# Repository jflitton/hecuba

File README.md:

# Hecuba

A read-only imager for Priam DISKOS 8-inch Winchester drives, talking to the
drive over its native PRIAM 50-pin interface. Three parts: a small interface
board, firmware for the Raspberry Pi Pico 2 W that plugs into it, and host-side
Python tools that image the drive, recover damaged sectors offline, and walk
the recovered filesystem.

It was built to recover a Priam 3450 pulled from an Intel Multibus development
system (iSBC 215 controller, iRMX-86), and has imaged that drive in full. The
name: Hecuba was queen of Troy and wife of Priam.

## For data preservationists

If you have a Priam DISKOS 8-inch drive (a 3450, or likely a 7050) whose
contents you want to archive, email <jeff@flitton.dev>. I have a handful of
assembled Hecuba boards and can send you one. I am also glad to help with the
imaging and recovery, and to answer questions about the drive or its interface.

## Layout

| Directory | Contents | README |
|---|---|---|
| `hardware/` | KiCad project for the interface board: schematic, layout, BOM, measured termination values, 50-pin pinout | [hardware/README.md](hardware/README.md) |
| `firmware/` | Pico 2 W firmware: PRIAM register bus, PIO/DMA track capture, USB serial console | [firmware/README.md](firmware/README.md) |
| `software/` | Host tools: whole-drive imaging, three offline recovery passes, iSBC 215 sector decoder, iRMX-86 filesystem walker, defect map | [software/README.md](software/README.md) |

## Why it exists

These drives have a unique interface that resembles SASI at first glance but
is distinctly different.

- The heads move only on the drive's own command. There is no STEP line; a seek
  is a register write over the ribbon. The drive must be powered, spun up, and
  answering before it will read anything.
- The interface is recovered NRZ data plus clock on RS-422 pairs at 6.4 Mbit/s,
  not raw flux. A flux imager has nothing to read.

Acquisition and decoding are kept separate: capture each track once, cleanly,
then decode and repair offline, minimizing drive wear.

## Workflow

1. Build the board (`hardware/`). Rev 0.9A is fabricated and assembled.
2. Build and flash the firmware (`firmware/`), then bring the drive up from the
   USB serial console: `up`, `id`, `pins`, `stair`.
3. Image the drive with `software/sweep.py`, which drives that console and
   writes per-track sector images plus every raw capture.
4. Recover remaining sectors offline with `vote_repair.py`, `rescue.py`, and
   `deep_rescue.py`.
5. Walk the volume with `irmx_fs.py`, and attribute unrecovered sectors with
   `defect_map.py`.

## Read-only

The board has no copper on the write lines, and the firmware has no code path
that asserts WRITE GATE. Writing to a disk would require modifying the board.

## Scope

The sector decoder and filesystem walker target what this drive held: the Intel
iSBC 215 512-byte sector format and iRMX-86 named volumes. The board and
firmware are format-agnostic and capture raw bits from any drive with the PRIAM
interface. Termination values in `hardware/` were measured on one drive;
measure yours before populating.

Only the DISKOS 3450 has been tested. The DISKOS 7050 shares the same
interface, electrical spec, and service manual, so the board and firmware
should work on it as well, unconfirmed. The 7050 has 1049 cylinders to the
3450's 525, and that count is hardcoded in `firmware/include/priam_proto.h`
and `software/sweep.py`; the `id` command also expects the 3450's ID code.

No disk contents are part of this repository.

## License

The firmware and software are released under the MIT License, see
[LICENSE](LICENSE). The hardware design under `hardware/` is released under the
CERN Open Hardware Licence Version 2, Permissive (CERN-OHL-P-2.0), see
[hardware/LICENSE](hardware/LICENSE).

Both licenses allow commercial use, and both require that the copyright notice
and license text stay with copies and derived works. Both disclaim all
warranties: the software, the firmware, the design files, and any board built
from them are provided as is, and the risk of building and using them is
yours. Vendor symbol and footprint files under `hardware/lib/` are Texas
Instruments' and are not covered by either license.

## Reference documents

- [Priam 8-inch Winchester maintenance manual, July 1982](https://bitsavers.org/pdf/priam/Priam8_Maint_Jul82.pdf),
  and its [drawings volume](https://bitsavers.org/pdf/priam/Priam8_Maint_Drawings_Jul82.pdf)
  (schematics; an [800 dpi scan](https://bitsavers.org/pdf/priam/Priam8_Maint_Drawings_800dpi_Jul82.pdf) is also there)
- [Intel iSBC 215 Winchester Disk Controller Hardware Reference Manual,
  121593-002, September 1981](https://bitsavers.org/pdf/intel/iSBC/121593-002_iSBC_215_Winchester_Disk_Controller_Hardware_Reference_Manual_Sep1981.pdf)
- David Gesswein's excellent [mfm](https://www.pdp8online.com/mfm/) project, which documents the iSBC 215 sector format

## Author

Jeff Flitton, <jeff@flitton.dev>

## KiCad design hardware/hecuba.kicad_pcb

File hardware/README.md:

# Hecuba hardware

KiCad project for the Hecuba interface board. It sits between a Priam DISKOS
8-inch Winchester drive's native 50-pin interface and a Raspberry Pi Pico 2 W
(ref `A1`), which runs the firmware in `../firmware`. Rev 0.9A is fabricated,
assembled, and has imaged a full Priam 3450. Read-only by design.

## Why a custom board

The Priam 3450 (about 35 MB, 3,600 RPM, 5 heads, 525 cylinders) fits none of
the usual readers.

- No STEP line. Heads are positioned by a closed-loop voice-coil servo under an
  on-board 8035. A seek is a register write plus a Seek command, and the drive
  must be powered, spun up, and taking commands before it returns a bit.
- Not a flux interface. The drive does its own data separation and outputs
  recovered NRZ data plus clock on RS-422 pairs at 6.4 Mbit/s.
- The sector format belongs to the controller that wrote the disk (an Intel
  iSBC 215 here), not to the drive. Decoding happens offline in `../software`.
- Not SASI, despite the 50-pin ribbon and 8-bit active-low bus. PRIAM has no
  REQ/ACK handshake and carries read data on separate differential pairs.

## Building one

| | |
|---|---|
| Board | 2 layers, 125 x 104 mm, 1.6 mm. Signals on top; bottom is a ground pour with +5 V and +3.3 V routed through it as 1 mm paths |
| Tracks and vias | 0.2 mm signal, 1.0 mm power. Vias 0.6 mm / 0.3 mm hole (1.0 / 0.6 on power) |
| Smallest features | 0.2 mm track, 0.3 mm hole, 0.5 mm copper to edge |
| Packages | SOIC and SOT-23-6 ICs, 0805 passives. Hand-solderable in about an hour |
| Mounting | Four 3 mm plated holes, grounded |
| Parts list | `bom/bom.csv`, with a column for parts deliberately left unpopulated |
| Placement guide | `bom/ibom.html`, interactive; click a part to see where it goes |

All ICs are current-production TI parts as of 2026. Gerbers are plotted from
KiCad when needed and are not committed.

Routing rules for a respin:

- Only READ DATA and READ/REF CLOCK need care. Route each as a tight parallel
  pair over unbroken ground, and keep the two pairs apart. No impedance control
  and no length matching (the skew budget at 6.4 Mbit/s is about 170 mm).
- Everything else is slow. Keep the 8 data-bus lines grouped.
- Damping resistors at the source, termination at the receiver, and each
  100 nF capacitor hard against its power pin with its own ground via.

## Parts

| Ref | Part | Function | Datasheet |
|---|---|---|---|
| A1 | Pico 2 W (RP2350) | Controller. Powers the board over USB | [raspberrypi.com](https://datasheets.raspberrypi.com/picow/pico-2-w-datasheet.pdf) |
| U1 | SN74LVC4245A | 8-bit data bus, bidirectional. Direction set by the Pico (GP8) | [ti.com](https://www.ti.com/lit/ds/symlink/sn74lvc4245a.pdf) |
| U2 | SN74LVC4245A | Outbound control lines: address, strobes, head select, read gate. Direction strapped | [ti.com](https://www.ti.com/lit/ds/symlink/sn74lvc4245a.pdf) |
| U3 | SN74LVC14A | Schmitt-trigger inverters on INDEX, READY, SECTOR MARK | [ti.com](https://www.ti.com/lit/ds/symlink/sn74lvc14a.pdf) |
| U4 | AM26LV32E | RS-422 receivers for READ DATA and READ/REF CLOCK. Receive only | [ti.com](https://www.ti.com/lit/ds/symlink/am26lv32e.pdf) |
| U5 | SN74LVC1T45 | -RESET driver. Direction strapped | [ti.com](https://www.ti.com/lit/ds/symlink/sn74lvc1t45.pdf) |
| J1 | 2x25 IDC header | 50-pin ribbon to the drive | |

## Termination

Measured on one drive. Measure yours before populating. The manual's generic
values assume the controller terminates everything; this drive terminates most
of the bus internally. Values were measured at the connector with the drive
unpowered and the ribbon off.

| Part | Value | Fitted | Reason |
|---|---|---|---|
| R1-R16, R28 | 0 ohm | yes | Series damping on outbound lines. The drive terminates this bus at about 179 ohm; even 33 ohm in series lifts a logic low to about 0.72 V against a 0.8 V threshold. Fit 10 ohm or less only if a scope shows overshoot |
| R17 / R20 | 220 / 330 ohm | yes | INDEX pull-up and pull-down. INDEX measured open at the drive. Settles near 3.0 V released |
| R18-R19 / R21-R22 | 220 / 330 ohm | no | READY and SECTOR MARK are pulled up inside the drive (130 / 175 ohm measured). Fit only if J1 pin 28 is left unpowered |
| R26 | 1 k | yes | Bias across the CLOCK pair, which measured 95 ohm. 100 ohm here would load the pair to 49 ohm |
| R27 | 100 ohm | yes | Termination across the DATA pair, which measured 252 ohm |
| R29 | 10 k | yes | Pull-up on GP17 (-RESET). Holds reset deasserted through boot |
| C1-C8 | 100 nF | yes | Decoupling, one per power pin |
| C9 / C10 | 10 uF | yes | Bulk on each rail at the Pico's power pins |
| JP1 | 2-pin header | shunt open | +5 V to J1 pin 28 (terminator power). Not needed on the drive tested |

## 50-pin connector (J1)

| Signal | Pin | Direction | Connects to |
|---|---|---|---|
| DBUS 0-7 | 2-9 | both | U1 via R1-R8 |
| -READ GATE | 11 | to drive | U2 via R9 |
| -RESET | 13 | to drive | U5 via R28 |
| -WRITE GATE | 15 | to drive | not connected |
| -RD / -WR | 17 / 18 | to drive | U2 via R10 / R11 |
| +AD 1 / +AD 0 | 19 / 20 | to drive | U2 via R12 / R13 |
| -DRIVE SELECT 1 | 22 | to drive | ground (always selected) |
| -DRIVE SELECT 2-4 | 23-25 | to drive | not connected |
| +5 V to terminator | 28 | power | JP1 (open) |
| -HEAD SELECT 4 / 2 / 1 | 29 / 30 / 31 | to drive | U2 via R14 / R15 / R16 |
| -INDEX | 33 | from drive | U3, with R17 / R20 |
| -READY | 35 | from drive | U3 |
| -SECTOR MARK | 37 | from drive | U3 |
| WRITE DATA pair | 39 / 40 | to drive | not connected |
| WRITE CLOCK pair | 42 / 43 | to drive | not connected |
| READ/REF CLOCK pair | 45 / 46 | from drive | U4, R26 across |
| READ DATA pair | 48 / 49 | from drive | U4, R27 across |

Ground pins 1, 10, 12, 14, 16, 21, 26, 27, 32, 34, 36, 38, 41, 44, 47, 50
connect to the ground plane.

## Power

- Drive rails (+24 V, +5 V, -5 V, -12 V, about 100 W total) come from a bench
  supply into the drive's own connector. The board neither carries nor senses
  them. Current-limit and watch +24 V at power-up; it runs the spindle and the
  voice coil.
- Board rails come from the Pico's USB. VBUS (pin 40) feeds the drive-facing
  side of the translators and the status pull-ups. The Pico's 3.3 V regulator
  (pin 36) feeds the Pico-facing side.
- Board draw is about 250 mA idle and 400 to 600 mA peak (the radio spikes on
  transmit). Use a 1.5 A supply or powered hub.

Power the Pico first, then the drive, and do not replug USB while the drive is
powered. Until firmware init runs, the Pico's pins are inputs with pull-downs,
which asserts every active-low control line through U2. Only -RESET is
protected in hardware (R29).

## Noteworthy facts

- **Write lines have no copper.** WRITE GATE, WRITE DATA, and WRITE CLOCK
  appear on the connector symbol only. No trace, no resistor. Writing would
  require adding wires to the board. The drive's own Write Enable switch is
  also off, and its internal terminator holds WRITE GATE deasserted.
- **The drive is 5 V TTL; the RP2350 is 3.3 V and not 5 V tolerant.** Every
  signal crosses a translator. Net names carry the level: `DBUS0` on the drive
  side, `DBUS0_3V3` on the Pico side.
- **Status lines invert.** U3 inverts, so INDEX, READY, and SECTOR MARK read
  active-high at the Pico while every other PRIAM signal is active-low. The
  schematic writes active-low nets as `~{NAME}`; the drive manual uses a
  leading minus. The full per-line chain is in
  `../firmware/include/board_pins.h`.
- **U3 is a Schmitt trigger on purpose.** The drive's status outputs are
  open-collector 75462s with slow RC rising edges. Hysteresis turns each into
  one clean transition. The drive's own end uses 74LS14s for the same reason.
- **U4 is the E variant on purpose.** AM26LV32E adds hysteresis and an
  open-input fail-safe, so the read pairs hold a defined level before READ GATE
  asserts and before the drive's clock recovery locks.
- **R29 is load-bearing.** U5 has no output enable and follows GP17 from
  power-on, and the RP2350 boots GP17 as an input with a pull-down. Without
  R29 every power-up would reset the drive.
- **DRIVE SELECT 1 is tied to ground.** One drive, permanently selected, no
  chip-select GPIO. The data bus still only drives back during a read strobe.
- **Unused U3 and U4 inputs are tied off.** Floating Schmitt or differential
  inputs oscillate.
- **R26 and R27 differ by 10x** for two pairs on the same connector. Only
  measurement finds that.

## Files

| Path | Contents |
|---|---|
| `hecuba.kicad_pro` | Project settings, net classes, design rules |
| `hecuba.kicad_sch` | Schematic, one sheet |
| `hecuba.kicad_pcb` | Board layout |
| `hecuba.kicad_prl` | KiCad UI state |
| `hecuba.kicad_sym` | Five project symbols. `PRIAM_50` is the drive connector with real PRIAM signal names |
| `footprints.pretty/` | Footprints for the four ICs, registered by `fp-lib-table` so the project opens standalone |
| `fp-lib-table` | Points KiCad at the folder above |
| `lib/<PART>/` | Vendor symbol and footprint downloads per chip, untouched. Datasheets are linked from the parts table, not stored here |
| `bom/bom.csv` | Parts list with populate / do-not-populate column |
| `bom/ibom.html` | Interactive BOM |

`.gitignore` covers KiCad backups and netlist output.

## License

CERN Open Hardware Licence Version 2, Permissive (CERN-OHL-P-2.0). The full
text is in [LICENSE](LICENSE). Keep the copyright and license notices with any
copy or derivative of the design files, and on boards where practicable (the
silkscreen already carries the author line). The design is provided as is, with
no warranty, and the risk of building and using a board from it is yours.

Files under `lib/<PART>/` are Texas Instruments vendor downloads under TI's own
terms and are not covered by this license.

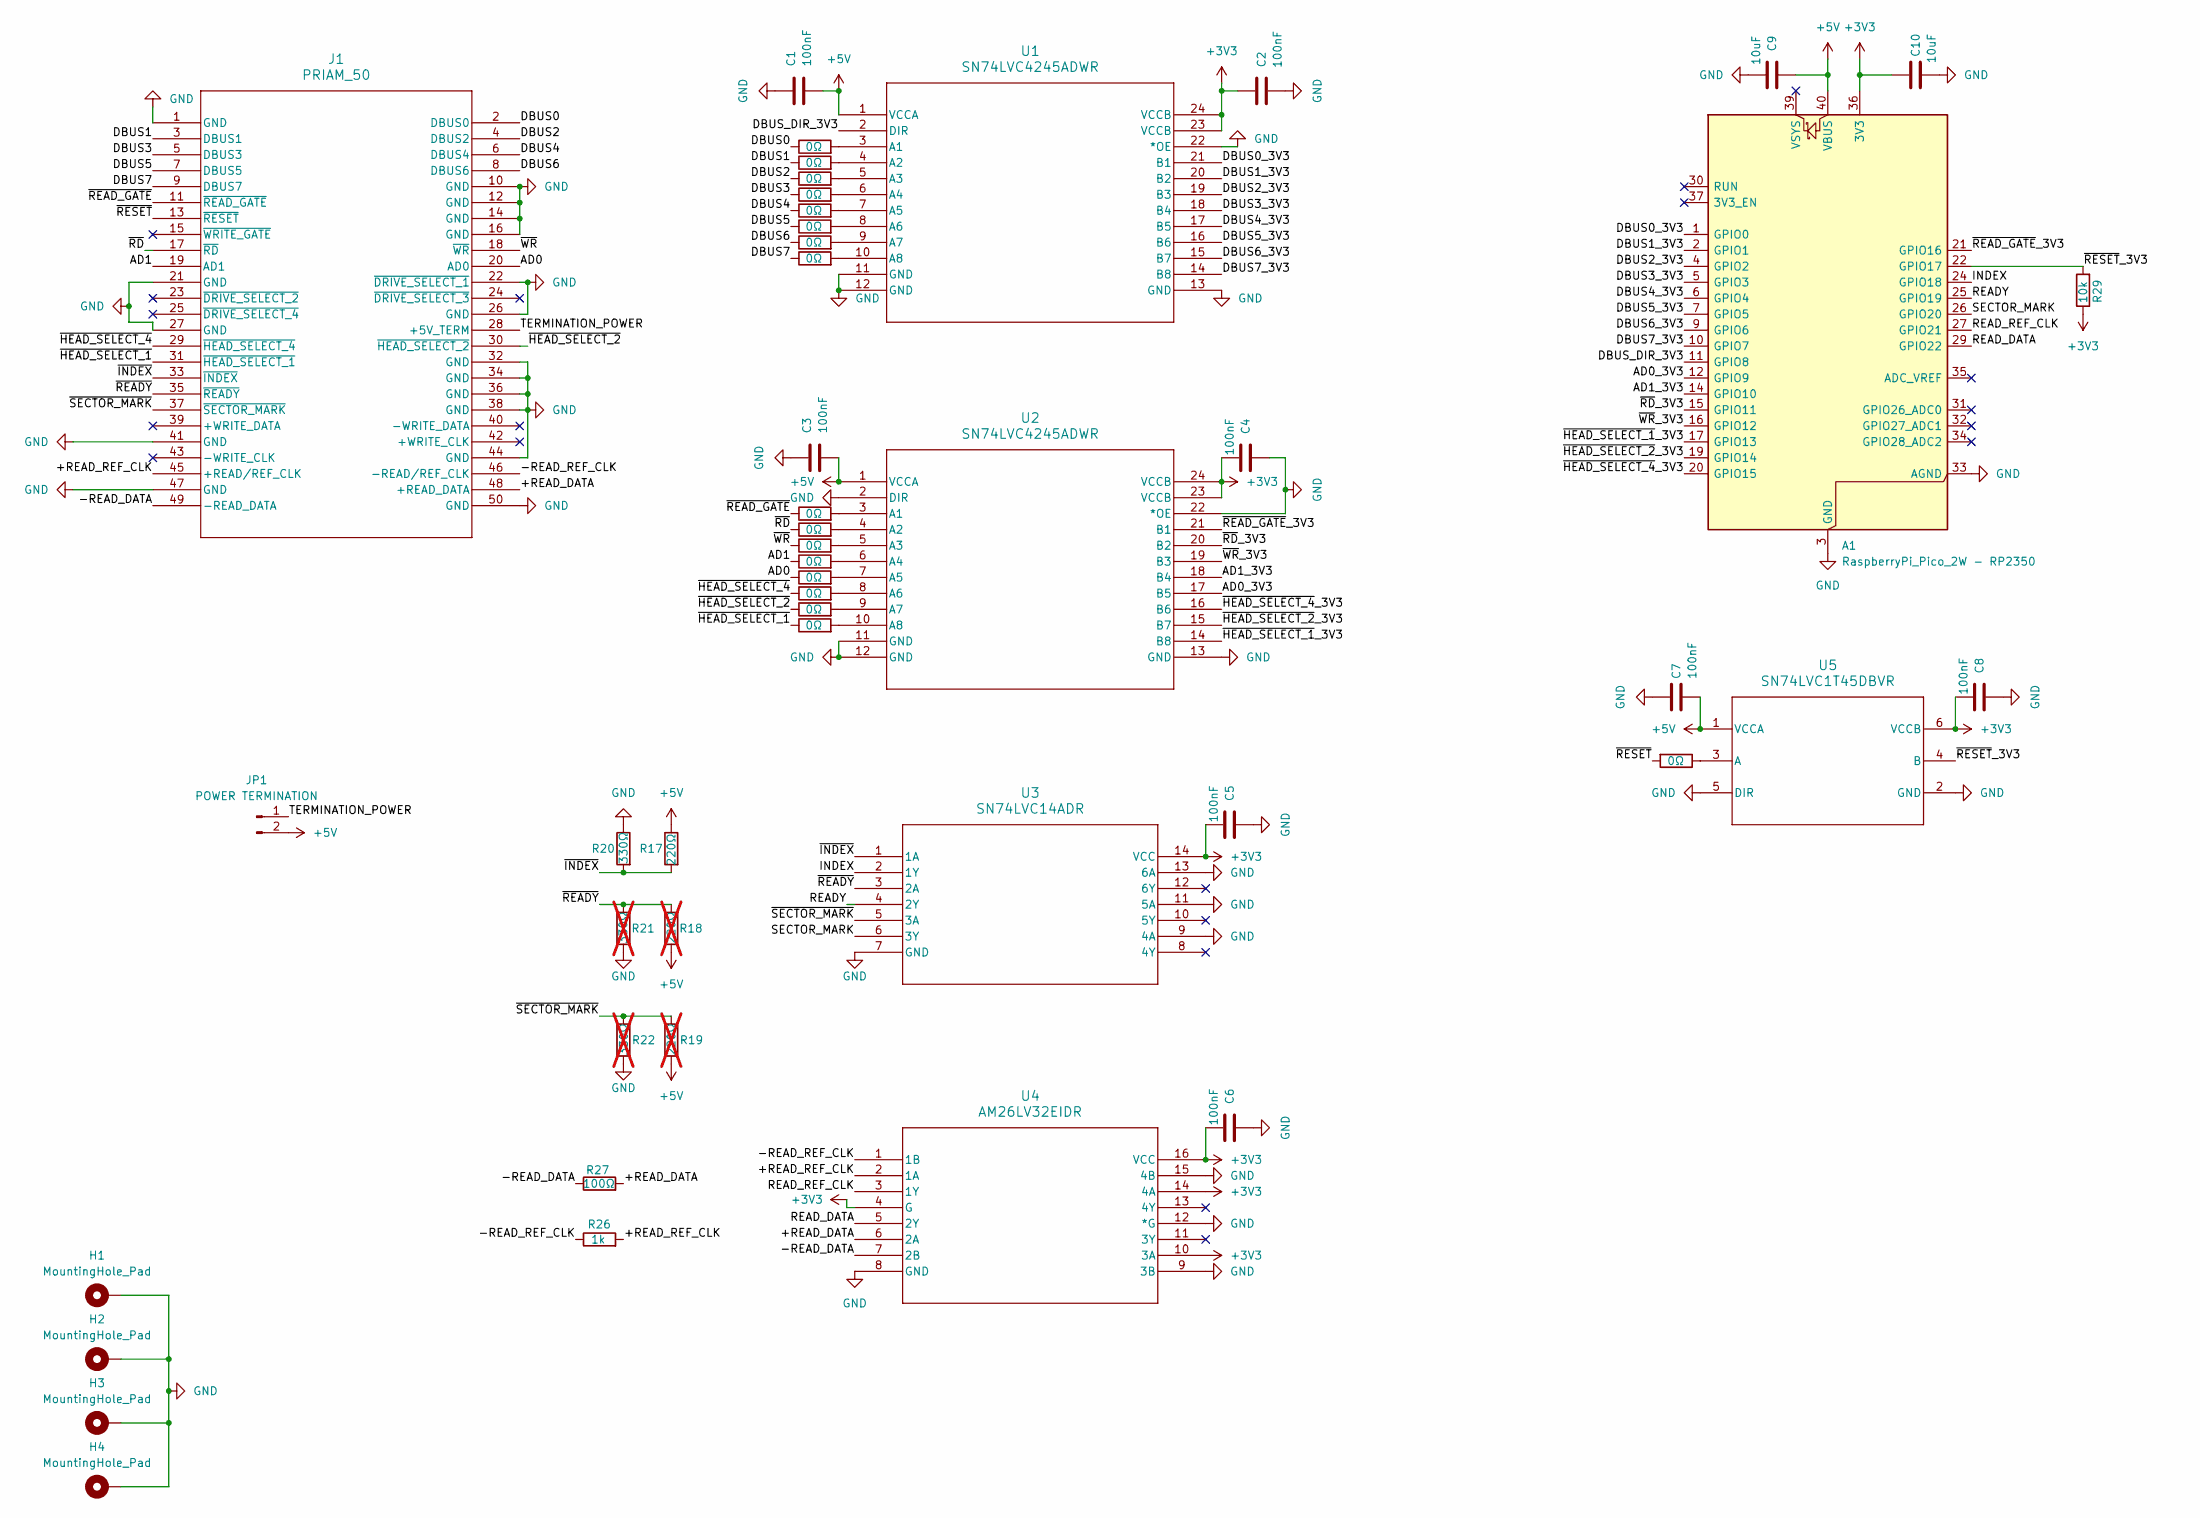
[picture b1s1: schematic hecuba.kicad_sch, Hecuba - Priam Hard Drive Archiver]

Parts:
A1: RaspberryPi_Pico_2W - RP2350; RaspberryPi_Pico_W_SMD_HandSolder
C1, C2, C3, C4, C5, C6, C7, C8: 100nF; C_0805_2012Metric_Pad1.18x1.45mm_HandSolder
C9, C10: 10uF; C_0805_2012Metric_Pad1.18x1.45mm_HandSolder
H1, H2, H3, H4: MountingHole_Pad; MountingHole_3mm_Pad
J1: PRIAM_50; IDC-Header_2x25_P2.54mm_Vertical
JP1: POWER TERMINATION; PinHeader_1x02_P2.54mm_Vertical
R1, R2, R3, R4, R5, R6, R7, R8, R9, R10, R11, R12, R13, R14, R15, R16, R28: 0Ω; R_0805_2012Metric_Pad1.20x1.40mm_HandSolder
R17: 220Ω; R_0805_2012Metric_Pad1.20x1.40mm_HandSolder
R18, R19: 220Ω; R_0805_2012Metric_Pad1.20x1.40mm_HandSolder; not fitted
R20: 330Ω; R_0805_2012Metric_Pad1.20x1.40mm_HandSolder
R21, R22: 330Ω; R_0805_2012Metric_Pad1.20x1.40mm_HandSolder; not fitted
R26: 1k; R_0805_2012Metric_Pad1.20x1.40mm_HandSolder
R27: 100Ω; R_0805_2012Metric_Pad1.20x1.40mm_HandSolder
R29: 10k; R_0805_2012Metric_Pad1.20x1.40mm_HandSolder
U1, U2: SN74LVC4245ADWR; DW24-M
U3: SN74LVC14ADR; D14-M
U4: AM26LV32EIDR; D16-M
U5: SN74LVC1T45DBVR; DBV0006A_M

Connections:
+3V3: A1.36 (3V3), C2.2, C4.2, C5.2, C6.2, C8.2, C10.1, R29.1, U1.23 (VCCB), U1.24 (VCCB), U2.23 (VCCB), U2.24 (VCCB), U3.14 (VCC), U4.4 (G), U4.10 (3A), U4.14 (4A), U4.16 (VCC), U5.6 (VCCB)
+5V: A1.40 (VBUS), C1.2, C3.2, C7.2, C9.1, JP1.2, R17.1, R18.2, R19.2, U1.1 (VCCA), U2.1 (VCCA), U5.1 (VCCA)
/+READ_DATA: J1.48 (+READ_DATA), R27.2, U4.6 (2A)
/+READ_REF_CLK: J1.45 (+READ/REF_CLK), R26.2, U4.2 (1A)
/-READ_DATA: J1.49 (-READ_DATA), R27.1, U4.7 (2B)
/-READ_REF_CLK: J1.46 (-READ/REF_CLK), R26.1, U4.1 (1B)
/AD0: J1.20 (AD0), R13.1
/AD0_3V3: A1.12 (GPIO9), U2.17 (B5)
/AD1: J1.19 (AD1), R12.1
/AD1_3V3: A1.14 (GPIO10), U2.18 (B4)
/DBUS0: J1.2 (DBUS0), R1.1
/DBUS0_3V3: A1.1 (GPIO0), U1.21 (B1)
/DBUS1: J1.3 (DBUS1), R2.1
/DBUS1_3V3: A1.2 (GPIO1), U1.20 (B2)
/DBUS2: J1.4 (DBUS2), R3.1
/DBUS2_3V3: A1.4 (GPIO2), U1.19 (B3)
/DBUS3: J1.5 (DBUS3), R4.1
/DBUS3_3V3: A1.5 (GPIO3), U1.18 (B4)
/DBUS4: J1.6 (DBUS4), R5.1
/DBUS4_3V3: A1.6 (GPIO4), U1.17 (B5)
/DBUS5: J1.7 (DBUS5), R6.1
/DBUS5_3V3: A1.7 (GPIO5), U1.16 (B6)
/DBUS6: J1.8 (DBUS6), R7.1
/DBUS6_3V3: A1.9 (GPIO6), U1.15 (B7)
/DBUS7: J1.9 (DBUS7), R8.1
/DBUS7_3V3: A1.10 (GPIO7), U1.14 (B8)
/DBUS_DIR_3V3: A1.11 (GPIO8), U1.2 (DIR)
/INDEX: A1.24 (GPIO18), U3.2 (1Y)
/READY: A1.25 (GPIO19), U3.4 (2Y)
/READ_DATA: A1.29 (GPIO22), U4.5 (2Y)
/READ_REF_CLK: A1.27 (GPIO21), U4.3 (1Y)
/SECTOR_MARK: A1.26 (GPIO20), U3.6 (3Y)
/TERMINATION_POWER: J1.28 (+5V_TERM), JP1.1
/~HEAD_SELECT_1: J1.31 (~HEAD_SELECT_1), R16.1
/~HEAD_SELECT_1_3V3: A1.17 (GPIO13), U2.14 (B8)
/~HEAD_SELECT_2: J1.30 (~HEAD_SELECT_2), R15.1
/~HEAD_SELECT_2_3V3: A1.19 (GPIO14), U2.15 (B7)
/~HEAD_SELECT_4: J1.29 (~HEAD_SELECT_4), R14.1
/~HEAD_SELECT_4_3V3: A1.20 (GPIO15), U2.16 (B6)
/~INDEX: J1.33 (~INDEX), R17.2, R20.2, U3.1 (1A)
/~RD: J1.17 (~RD), R10.1
/~RD_3V3: A1.15 (GPIO11), U2.20 (B2)
/~READY: J1.35 (~READY), R18.1, R21.1, U3.3 (2A)
/~READ_GATE: J1.11 (~READ_GATE), R9.1
/~READ_GATE_3V3: A1.21 (GPIO16), U2.21 (B1)
/~RESET: J1.13 (~RESET), R28.2
/~RESET_3V3: A1.22 (GPIO17), R29.2, U5.4 (B)
/~SECTOR_MARK: J1.37 (~SECTOR_MARK), R19.1, R22.1, U3.5 (3A)
/~WR: J1.18 (~WR), R11.1
/~WR_3V3: A1.16 (GPIO12), U2.19 (B3)
GND: A1.3 (GND), A1.8 (GND), A1.13 (GND), A1.18 (GND), A1.23 (GND), A1.28 (GND), A1.33 (AGND), A1.38 (GND), C1.1, C2.1, C3.1, C4.1, C5.1, C6.1, C7.1, C8.1, C9.2, C10.2, H1.1 (1_1), H2.1 (1_1), H3.1 (1_1), H4.1 (1_1), J1.1 (GND), J1.10 (GND), J1.12 (GND), J1.14 (GND), J1.16 (GND), J1.21 (GND), J1.22 (~DRIVE_SELECT_1), J1.26 (GND), J1.27 (GND), J1.32 (GND), J1.34 (GND), J1.36 (GND), J1.38 (GND), J1.41 (GND), J1.44 (GND), J1.47 (GND), J1.50 (GND), R20.1, R21.2, R22.2, U1.11 (GND), U1.12 (GND), U1.13 (GND), U1.22 (*OE), U2.2 (DIR), U2.11 (GND), U2.12 (GND), U2.13 (GND), U2.22 (*OE), U3.7 (GND), U3.9 (4A), U3.11 (5A), U3.13 (6A), U4.8 (GND), U4.9 (3B), U4.12 (*G), U4.15 (4B), U5.2 (GND), U5.5 (DIR)
unnamed: R1.2, U1.3 (A1)
unnamed: R2.2, U1.4 (A2)
unnamed: R3.2, U1.5 (A3)
unnamed: R4.2, U1.6 (A4)
unnamed: R5.2, U1.7 (A5)
unnamed: R6.2, U1.8 (A6)
unnamed: R7.2, U1.9 (A7)
unnamed: R8.2, U1.10 (A8)
unnamed: R9.2, U2.3 (A1)
unnamed: R10.2, U2.4 (A2)
unnamed: R11.2, U2.5 (A3)
unnamed: R12.2, U2.6 (A4)
unnamed: R13.2, U2.7 (A5)
unnamed: R14.2, U2.8 (A6)
unnamed: R15.2, U2.9 (A7)
unnamed: R16.2, U2.10 (A8)
unnamed: R28.1, U5.3 (A)

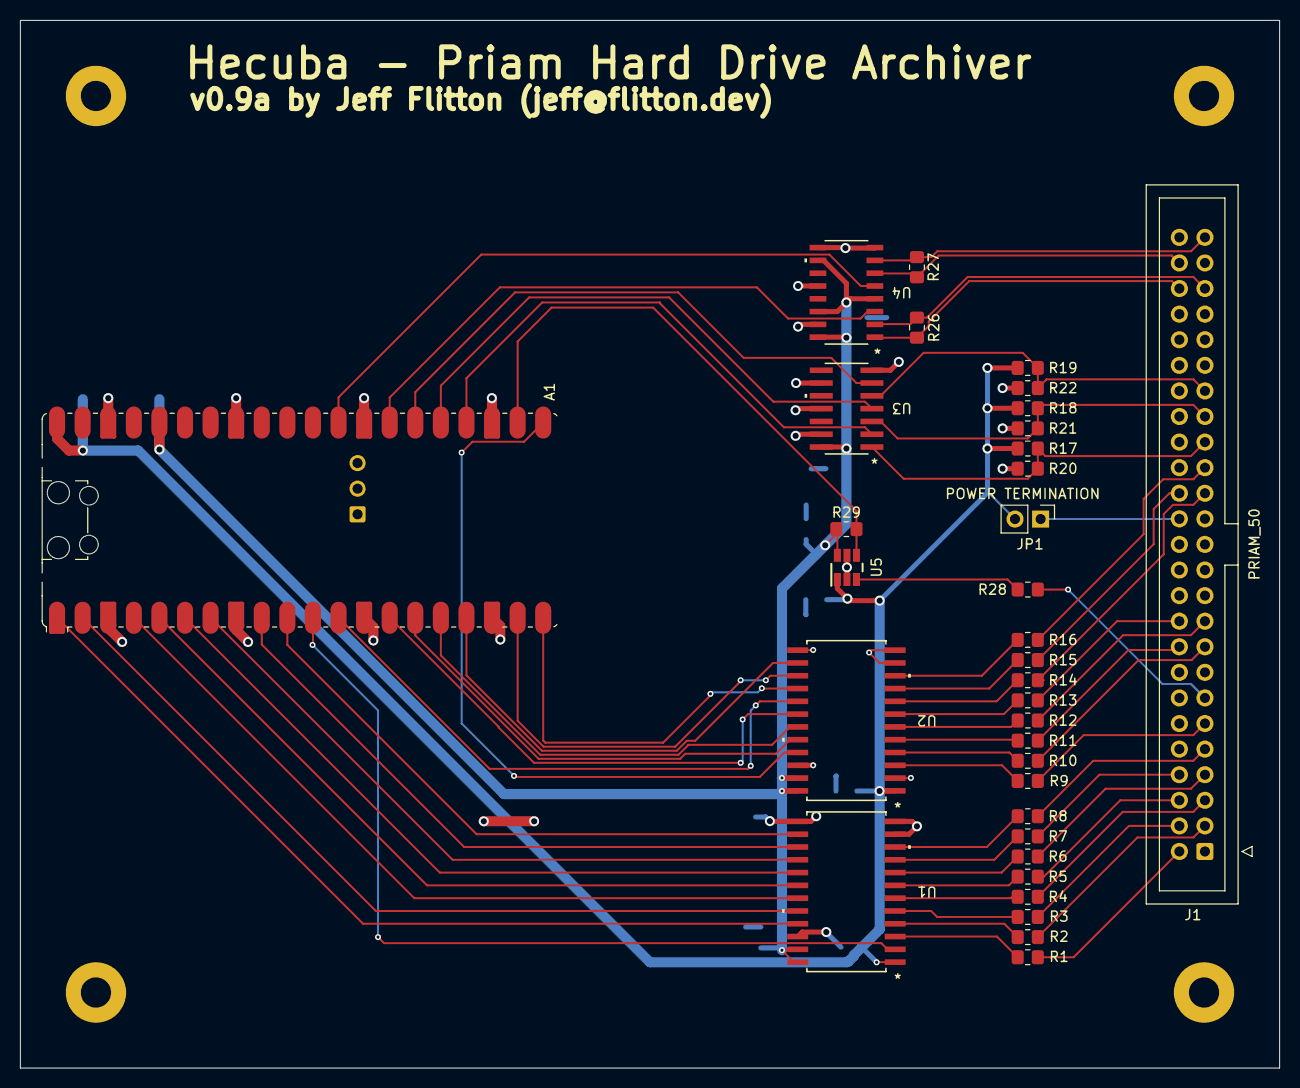
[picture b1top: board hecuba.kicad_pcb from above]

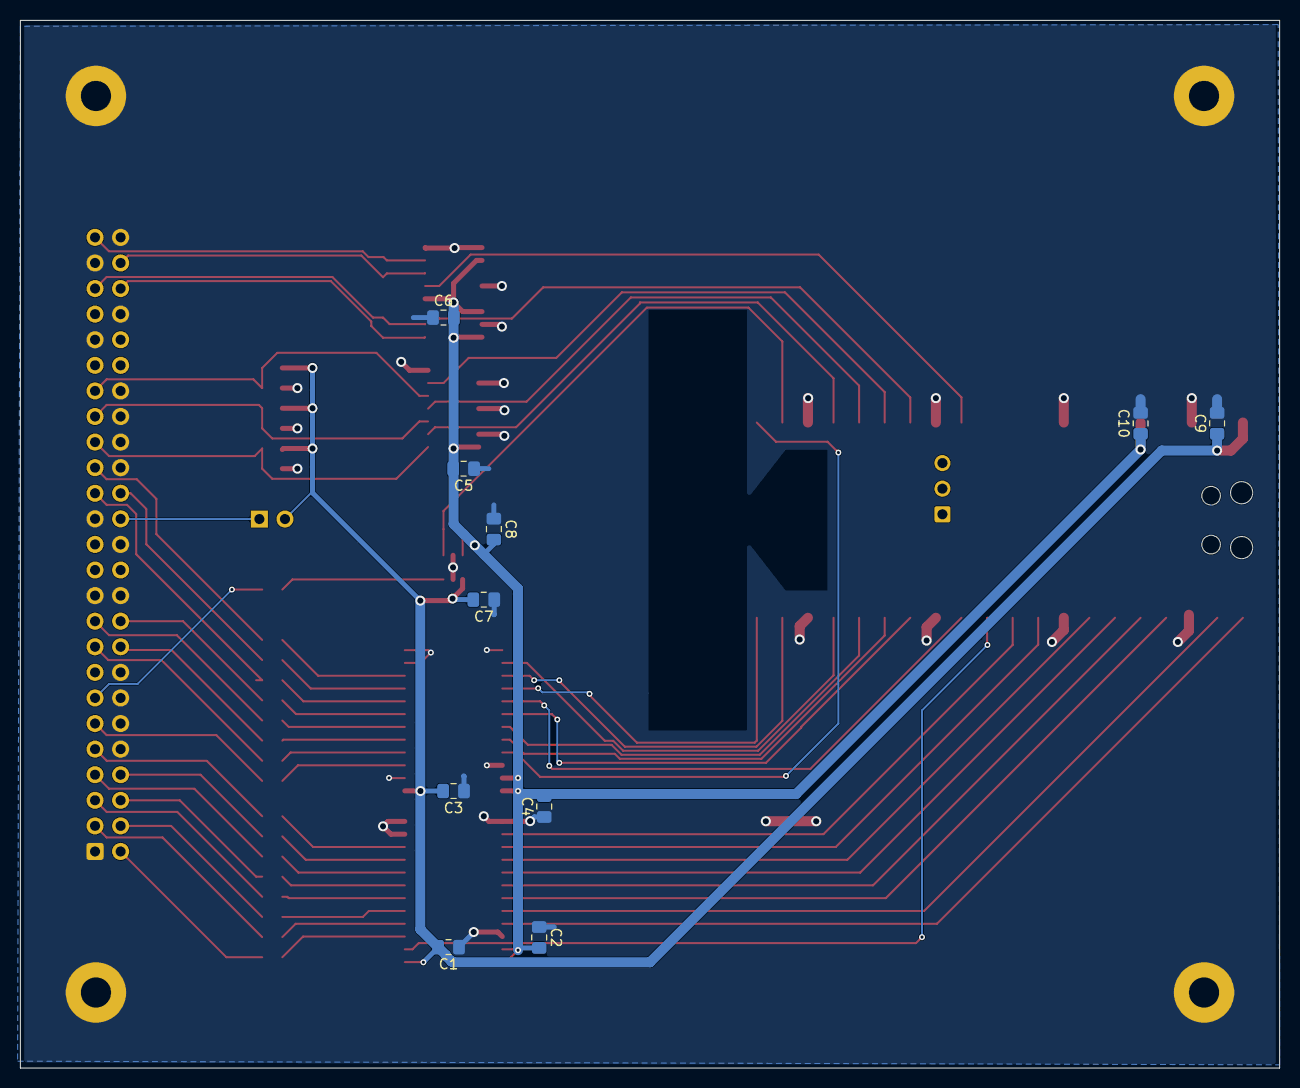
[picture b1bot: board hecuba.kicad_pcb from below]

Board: 2 copper layers, 125.0 x 104.0 mm, 48 parts (10 on the bottom side), 68 nets.

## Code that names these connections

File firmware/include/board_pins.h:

// board_pins.h - Hecuba controller GPIO map (RP2350 / Pico 2 W, ref A1)
//
// SINGLE SOURCE OF TRUTH for pin assignments, transcribed from the KiCad
// schematic in ../hardware. If the schematic changes, update this file to
// match it.
//
// ============================ POLARITY / SIGNAL CHAIN =======================
// Every line between the core and the 5 V drive is voltage-translated:
//
//   * DBUS0..7      U1  SN74LVC4245A  bidirectional, non-inverting.
//                       DIR = GP8 (PIN_DBUS_DIR): 0 => B->A (core drives = WRITE),
//                       1 => A->B (drive drives = READ). OE tied low (always on).
//   * Control outs  U2  SN74LVC4245A  DIR strapped low => always B->A,
//                       non-inverting. So a core GPIO level passes straight to the
//                       drive line. These drive lines are ACTIVE-LOW, therefore:
//                       assert  => drive GPIO LOW,  deassert => drive GPIO HIGH.
//                       (AD0/AD1 are plain logic levels, not active-low strobes.)
//   * -RESET        U5  SN74LVC1T45   DIR low => B->A, non-inverting. Active-low:
//                       GPIO LOW = reset asserted. R29 10k pulls GP17 high so the
//                       drive sees -RESET deasserted through boot (GP17 resets to
//                       input). Firmware drives GP17 output HIGH early to hold it.
//   * Status ins    U3  SN74LVC14A    INVERTING Schmitt. The drive's active-low
//                       -INDEX/-READY/-SECTOR MARK arrive at the core ACTIVE-HIGH:
//                       gpio_get(pin) == 1  means the signal is ASSERTED.
//   * READ DATA /   U4  AM26LV32E      RS-422 receiver, non-inverting -> clean
//     READ/REF CLK                     3V3 logic at the core.
//
// There is no -DRIVE SELECT GPIO: it is hard-tied asserted on the board for the
// single-drive setup (SIG-5), so firmware never drives a chip select.
// ============================================================================

#ifndef HECUBA_BOARD_PINS_H
#define HECUBA_BOARD_PINS_H

// ----- DBUS 0..7 : contiguous on GP0..GP7 (one byte, mask-addressable) ------
#define PIN_DBUS_BASE      0u
#define PIN_DBUS0          0u
#define PIN_DBUS7          7u
#define DBUS_MASK          (0xFFu << PIN_DBUS_BASE)   // 0x000000FF

// ----- Control / address outputs (via U2, non-inverting, active-low) --------
#define PIN_DBUS_DIR       8u    // U1 direction: 0=write(B->A), 1=read(A->B)
#define PIN_AD0            9u    // register select A0 (logic level)
#define PIN_AD1           10u    // register select A1 (logic level)
#define PIN_RD_N          11u    // -RD  strobe (assert = LOW)
#define PIN_WR_N          12u    // -WR  strobe (assert = LOW)
#define PIN_HS1_N         13u    // -HEAD SELECT 1 (assert = LOW)
#define PIN_HS2_N         14u    // -HEAD SELECT 2 (assert = LOW)
#define PIN_HS4_N         15u    // -HEAD SELECT 4 (assert = LOW)
#define PIN_READ_GATE_N   16u    // -READ GATE (assert = LOW)
#define PIN_RESET_N       17u    // -RESET via U5 (assert = LOW); R29 holds high

// ----- Status inputs (via U3, INVERTING -> active-HIGH at the core) ---------
#define PIN_INDEX         18u    // -INDEX       : core HIGH = index pulse
#define PIN_READY         19u    // -READY       : core HIGH = drive ready
#define PIN_SECTOR_MARK   20u    // -SECTOR MARK : core HIGH = sector mark

// ----- High-speed serial capture inputs (via U4 RS-422 rx) ------------------
#define PIN_READ_REF_CLK  21u    // recovered bit clock  (PIO `wait gpio`)
#define PIN_READ_DATA     22u    // recovered NRZ data   (PIO `in pins`)

// Aggregate masks for batch GPIO init.
#define CONTROL_OUT_MASK ( (1u<<PIN_DBUS_DIR) | (1u<<PIN_AD0) | (1u<<PIN_AD1) | \
                           (1u<<PIN_RD_N) | (1u<<PIN_WR_N) | \
                           (1u<<PIN_HS1_N) | (1u<<PIN_HS2_N) | (1u<<PIN_HS4_N) | \
                           (1u<<PIN_READ_GATE_N) | (1u<<PIN_RESET_N) )

#define STATUS_IN_MASK   ( (1u<<PIN_INDEX) | (1u<<PIN_READY) | (1u<<PIN_SECTOR_MARK) )

// Active-low control lines whose idle (deasserted) state is HIGH. -RESET is
// included so init parks it deasserted; DBUS_DIR/AD0/AD1 are excluded (they are
// logic levels, not active-low strobes; they default to a benign 0).
#define CONTROL_IDLE_HIGH_MASK ( (1u<<PIN_RD_N) | (1u<<PIN_WR_N) | \
                                 (1u<<PIN_HS1_N) | (1u<<PIN_HS2_N) | (1u<<PIN_HS4_N) | \
                                 (1u<<PIN_READ_GATE_N) | (1u<<PIN_RESET_N) )

#endif // HECUBA_BOARD_PINS_H
